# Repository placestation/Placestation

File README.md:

# PlaceStation

PlaceStation is a desktop pick-and-place machine for PCB assembly, manufactured by **Tejwani Industries Private Limited (TIPL)** in Maharashtra, India.

PlaceStation is a **derivative of the open-source [LumenPnP project by Opulo Inc.](https://github.com/opulo-inc/lumenpnp)** This repository contains the design source for all PlaceStation-specific modifications, released under the same open-source licenses as the upstream project.

If you are looking for the unmodified LumenPnP design files (frame, gantry, motherboard, feeders, etc.), please see the [upstream LumenPnP repository](https://github.com/opulo-inc/lumenpnp).

---

## What PlaceStation is

PlaceStation is sold as a finished pick-and-place machine for small electronics manufacturers, prototyping labs, and hardware startups in India and abroad. It is **based on LumenPnP v4** with the modifications listed below.

The PlaceStation product is sold commercially. The underlying design source — both upstream LumenPnP and the PlaceStation-specific modifications — is open source under CERN-OHL-W v2, GPLv3, and related licenses.

## Modifications in PlaceStation

For a detailed list see [CHANGES.md](./CHANGES.md). In brief:

1. **Sensorless homing (no endstop PCB)** — modified `x-motor-mount` removes the endstop cavity; X/Y endstop hardware is removed entirely; Marlin firmware patched for sensorless homing
2. **MGN12 linear rails throughout** — consistent rail size simplifies sourcing and assembly
3. **Motherboard manufactured by TIPL** — `mobo-REV05` design from Opulo, manufactured by TIPL with Opulo branding removed from silkscreen (license-compliant per CERN-OHL-W v2 §8.2)
4. **Datum board manufactured by TIPL** — Opulo's homing/calibration fiducial board, manufactured by TIPL with Opulo branding removed from silkscreen (same license-compliant debranding as the motherboard)
5. **Feeder PCB manufactured by TIPL** — Photon feeder board from Opulo, manufactured by TIPL with Opulo branding removed from silkscreen. This pass also inadvertently removed silkscreen artwork by Alethea "Stargirl" Flowers ([@theacodes](https://github.com/theacodes)) — see [CREDITS.md](./CREDITS.md#feeder-pcb-art-alethea-stargirl-flowers) for attribution
6. **Dual-color printed secondary fiducial** — replaces Opulo's PCB-based fiducial with a 3D-printed dual-extrusion part (black surround, white center dot)
7. **OpenPnP closed-loop feeder calibration plugin** — vision-based pocket calibration for Photon feeders, integrated into the `press-play-walk-away` branch of OpenPnP
8. **Custom Marlin firmware** — sensorless homing for X/Y plus speed-increment customizations

## Repository structure

```
.
├── README.md                        ← you are here
├── LICENSE                          ← umbrella license, points to per-component licenses
├── NOTICE                           ← attribution to all upstream projects
├── CHANGES.md                       ← detailed description of modifications
├── CREDITS.md                       ← all contributors and projects credited
├── licenses/
│   ├── CERN-OHL-W-v2.txt
│   ├── GPL-v3.txt
│   ├── MIT.txt
│   └── CC-BY-SA-4.0.txt
├── hardware/                        ← CAD modifications (CERN-OHL-W v2)
│   ├── x-motor-mount/
│   ├── mgn12-x-gantry/
│   └── secondary-fid-dual-color/
├── pcb/                             ← PCB modifications (CERN-OHL-W v2)
│   ├── mobo-REV05-debranded/
│   └── datum-board-debranded/
├── firmware/                        ← Firmware (GPLv3)
│   └── marlin/                      ← (placeholder, sources uploaded separately)
├── software/                        ← OpenPnP plugins and configs
│   └── openpnp/                     ← see also linked fork repository
└── reference/
    └── placestation-full-assembly/  ← Fusion exports of the whole machine (optional)
```

## How to buy a PlaceStation

Visit [placestation.in](https://placestation.in).

## How to build your own from this source

This repository contains only the **PlaceStation modifications**. To build a complete machine you also need the unmodified upstream LumenPnP files. The recommended flow is:

1. Clone the upstream LumenPnP repository: `git clone https://github.com/opulo-inc/lumenpnp`
2. Clone this repository: `git clone https://github.com/placestation/Placestation`
3. Use parts from the upstream repo unless this repo has a replacement for them
4. For firmware: see `firmware/marlin/README.md`
5. For software: see `software/openpnp/README.md`

We are a small team and cannot offer free build support. Commercial machines come with full assembly and support from TIPL.

## Licenses

This project uses multiple licenses for different components. See [LICENSE](./LICENSE) for the umbrella summary and [licenses/](./licenses/) for full license texts.

- **Hardware (CAD, PCB):** CERN-OHL-W v2
- **Firmware (Marlin fork):** GPLv3
- **Software (OpenPnP plugin):** GPLv3 (inherited from OpenPnP)
- **Software (PlaceStation tools and configs):** MIT
- **Documentation:** CC BY-SA 4.0

## Attribution

PlaceStation builds on the work of many open-source projects and individuals. See [CREDITS.md](./CREDITS.md) for the full list.

Particular thanks to:
- **Opulo Inc. / Stephen Hawes** for LumenPnP and the upstream Marlin fork
- **The OpenPnP project** and contributors, especially **Jorropo** for the `press-play-walk-away` branch
- **Richard Klingler** and **PapaJ** for the CP40 nozzle holder design
- **The Photon firmware project** for the Photon feeder protocol
- **Alethea "Stargirl" Flowers** ([@theacodes](https://github.com/theacodes)) for the original feeder PCB silkscreen artwork
- **The Marlin Firmware project** for the base firmware

## Contact

Tejwani Industries Private Limited
GSTIN: 27AALCT0935H1Z6
Maharashtra, India
Website: [placestation.in](https://placestation.in)

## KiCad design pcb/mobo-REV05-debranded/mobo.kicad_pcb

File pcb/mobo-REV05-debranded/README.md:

# mobo-REV05-debranded

PlaceStation motherboard — Opulo `mobo-REV05` design, manufactured by TIPL, with Opulo branding removed from the silkscreen layer.

## What changed

**Silkscreen only.** The Opulo wordmark and logo have been removed from the silkscreen layer per CERN-OHL-W v2 §8.2, which requires removal of upstream trademarks when redistributing under a different brand.

Schematic, electrical layout, copper layers, drill files, BOM, component values, and functionality are **identical to upstream `mobo-REV05`**. This is not a redesign.

## Files

| File | Format | Description |
|------|--------|-------------|
| `mobo.kicad_pcb` | KiCad PCB | Board layout source |
| `mobo.kicad_pro` | KiCad project | Project file |

## Manufacturing

This board is manufactured by Tejwani Industries Private Limited (TIPL) under the CERN-OHL-W v2 license, which explicitly permits commercial manufacturing of covered hardware (§4.1).

## License

CERN-OHL-W v2 — see [`../../licenses/CERN-OHL-W-v2.txt`](../../licenses/CERN-OHL-W-v2.txt)

**Upstream:** `mobo-REV05` originally designed by Opulo Inc. ([github.com/opulo-inc/lumenpnp](https://github.com/opulo-inc/lumenpnp)), CERN-OHL-W v2. This file is a silkscreen-only derivative.

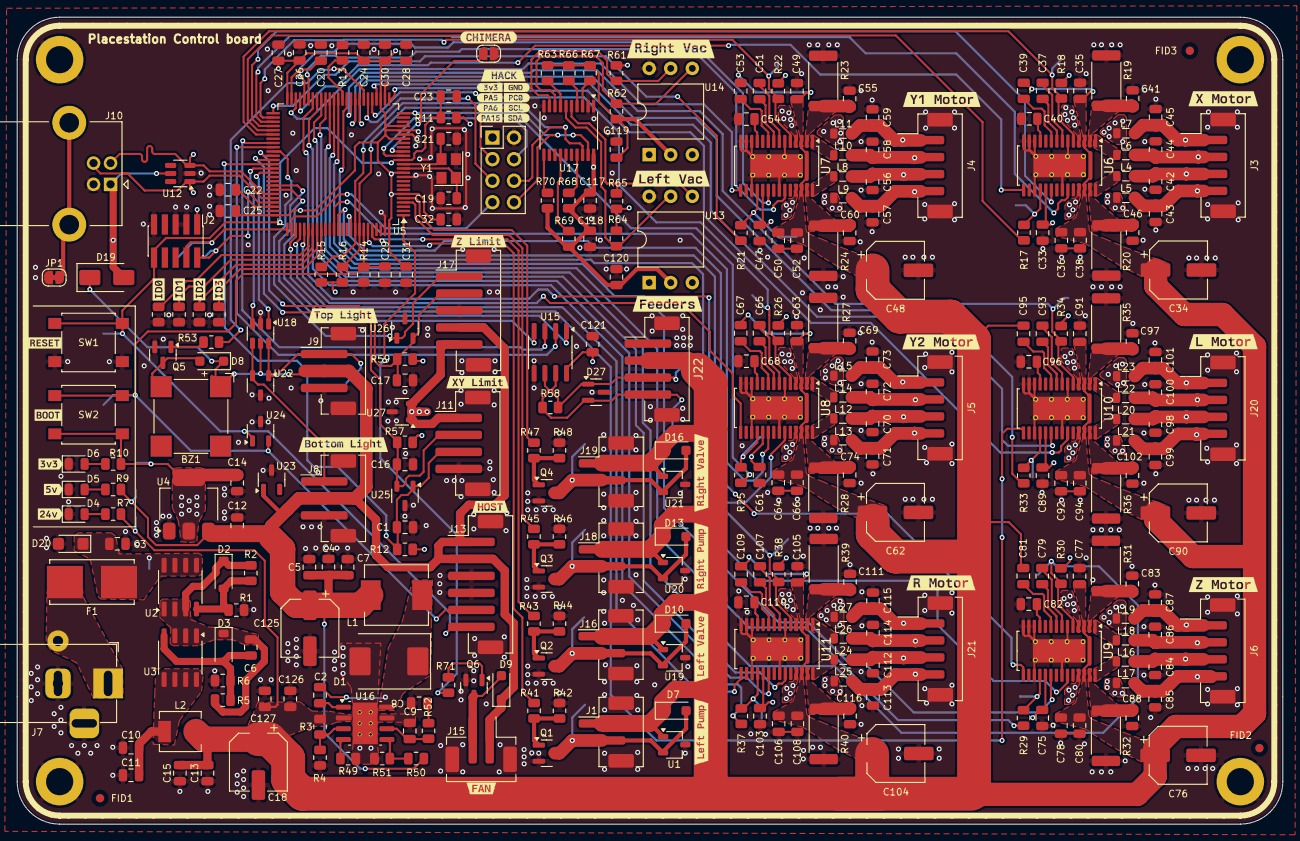
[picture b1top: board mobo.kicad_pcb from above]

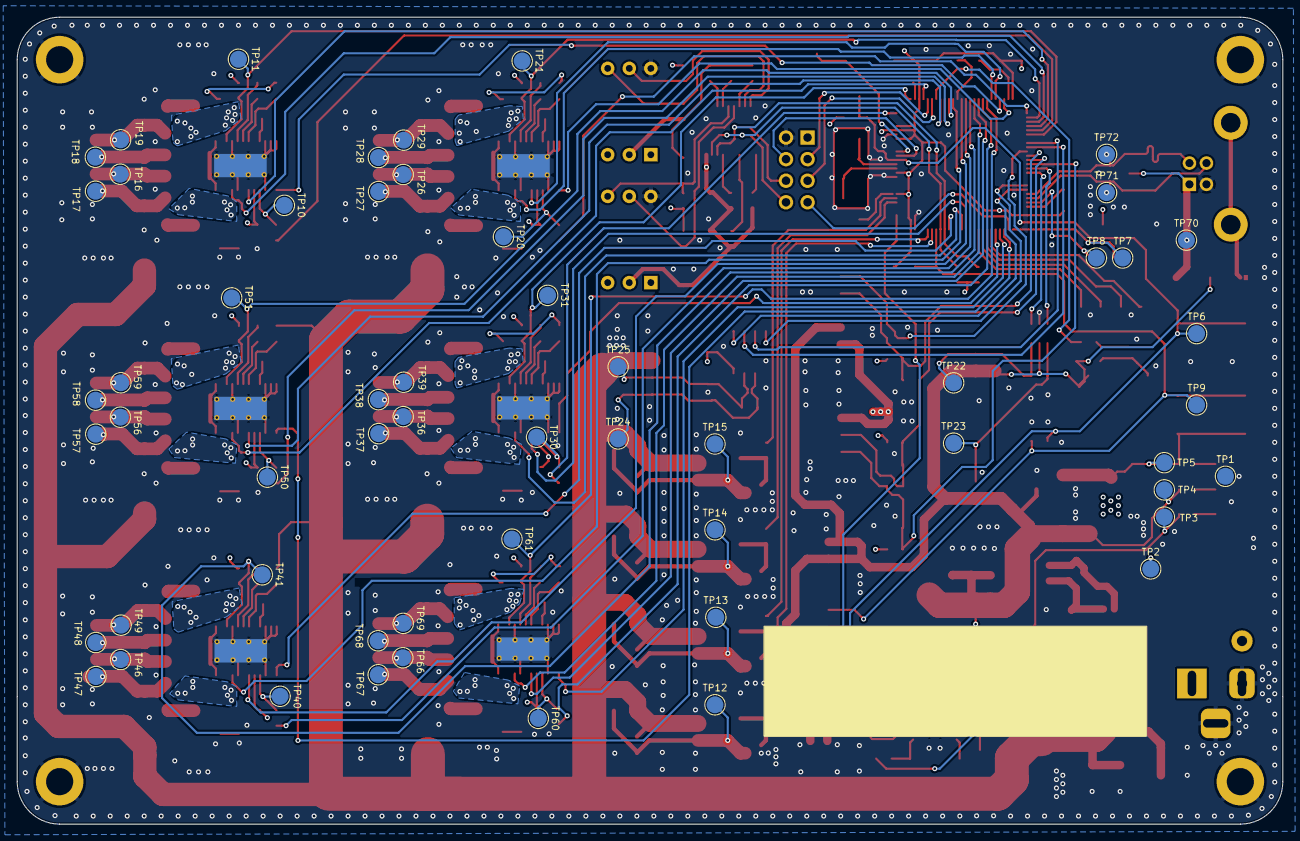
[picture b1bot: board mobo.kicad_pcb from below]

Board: 4 copper layers, 149.0 x 95.0 mm, 397 parts (56 on the bottom side), 206 nets.

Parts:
BZ1: Buzzer; MagneticBuzzer_CUI_CMT-8504-100-SMT
C1, C6, C16, C17, C23, C26, C27, C28, C29, C30, C31, C32, C33, C36, C38, C39, C41, C46, C47, C50, C52, C53, C55, C60, C61, C64, C66, C67, C69, C74, C75, C78, C80, C81, C83, C88, C89, C92, C94, C95, C97, C102, C103, C106, C108, C109, C111, C116, C117, C119, C120, C121: 100n; C_0805_2012Metric
C2: 0.1u; C_0805_2012Metric
C3, C4, C5, C7, C10, C11, C12, C13, C14, C15, C35, C49, C63, C77, C91, C105, C118, C126, C127: 10u; C_0805_2012Metric
C8: 4.7n; C_0805_2012Metric
C9: 47p; C_0805_2012Metric
C18, C34, C48, C62, C76, C90, C104, C125: 100u; CP_Elec_6.3x7.7
C19, C21: 10p; C_0805_2012Metric
C20, C22, C24, C25: 2u2; C_0805_2012Metric
C37, C51, C65, C79, C93, C107: 22n; C_0805_2012Metric
C40, C54, C68, C82, C96, C110: 4.7u; C_0805_2012Metric
C42, C43, C44, C45, C56, C57, C58, C59, C70, C71, C72, C73, C84, C85, C86, C87, C98, C99, C100, C101, C112, C113, C114, C115: 470p; C_0805_2012Metric
D1: B560C; D_SMC
D2, D3: BZT52C16; D_SOD-123
D4, D5, D6: Yellow; LED_0805_2012Metric
D7, D8, D9, D10, D13, D16: SM4007; D_SOD-123F
D19: SS34; D_SMA
D20: SMF28A; D_SMF
D27: SM712_SOT23; SOT-23
F1: Fuse; Fuseholder_Littelfuse_Nano2_154x
FID1, FID2, FID3: Fiducial; Fiducial_1mm_Mask2mm
H1, H2, H3, H4: MountingHole_Pad; MountingHole_3.2mm_M3_DIN965_Pad
J1, J16, J18, J19: FET; JST_PH_B2B-PH-SM4-TB_1x02-1MP_P2.00mm_Vertical
J2: SWD Header; PinHeader_2x05_P1.27mm_Vertical_SMD
J3, J4, J5, J6, J20, J21: MOTOR; JST_PH_B4B-PH-SM4-TB_1x04-1MP_P2.00mm_Vertical
J7: COMBO_POWER_JACK; BarrelJack_Horizontal
J8: BTM_LIGHT; JST_PH_B3B-PH-SM4-TB_1x03-1MP_P2.00mm_Vertical
J9: TOP_LIGHT; JST_PH_B3B-PH-SM4-TB_1x03-1MP_P2.00mm_Vertical
J10: USB_B; USB_B_Lumberg_2411_02_Horizontal
J11: XY_LIMIT; JST_PH_B4B-PH-SM4-TB_1x04-1MP_P2.00mm_Vertical
J13: HOST; JST_PH_B6B-PH-SM4-TB_1x06-1MP_P2.00mm_Vertical
J14: HACK_HEADER; PinHeader_2x04_P2.54mm_Vertical
J15: FAN; JST_PH_B2B-PH-SM4-TB_1x02-1MP_P2.00mm_Vertical
J17: Z_LIMIT; JST_PH_B5B-PH-SM4-TB_1x05-1MP_P2.00mm_Vertical
J22: FEEDERS; JST_PH_B4B-PH-SM4-TB_1x04-1MP_P2.00mm_Vertical
JP1: SHIELD_GND; SolderJumper-2_P1.3mm_Bridged_RoundedPad1.0x1.5mm
JP2: CHIMERA_JUMPER; SolderJumper-2_P1.3mm_Open_RoundedPad1.0x1.5mm
L1: 7.2u; L_Sunlord_MWSA0603S
L2: 2.2u; L_Sunlord_MWSA0402S
L4, L5, L6, L7, L8, L9, L10, L11, L12, L13, L14, L15, L16, L17, L18, L19, L20, L21, L22, L23, L24, L25, L26, L27: L_Ferrite; L_0805_2012Metric
Q1, Q2, Q3, Q4, Q5, Q6: AO3400A; SOT-23
R1, R3, R6, R7, R11, R13, R14, R18, R22, R26, R30, R34, R38, R42, R44, R46, R48, R51, R63, R66, R67, R68, R69, R70: 10k; R_0805_2012Metric
R2, R5, R15, R16: 4.7k; R_0805_2012Metric
R4, R9: 2.7k; R_0805_2012Metric
R8, R54, R55, R56: 0R; R_0805_2012Metric
R10, R17, R21, R25, R29, R33, R37: 1k; R_0805_2012Metric
R12, R57, R59: 10K; R_0805_2012Metric
R19, R20, R23, R24, R27, R28, R31, R32, R35, R36, R39, R40: 120m; R_2512_6332Metric
R41, R43, R45, R47, R58: 120; R_0805_2012Metric
R49: 243k; R_0805_2012Metric
R50: 53.6k; R_0805_2012Metric
R52: 16.9k; R_0805_2012Metric
R53, R71: 120R; R_0805_2012Metric
R61, R62, R64, R65: 4k7; R_0805_2012Metric
SW1, SW2: SW_Push; SW_SPST_B3S-1000
TP1, TP2, TP3, TP4, TP5, TP6, TP7, TP8, TP9, TP10, TP11, TP12, TP13, TP14, TP15, TP16, TP17, TP18, TP19, TP20, TP21, TP22, TP23, TP24, TP25, TP26, TP27, TP28, TP29, TP30, TP31, TP36, TP37, TP38, TP39, TP40, TP41, TP46, TP47, TP48, TP49, TP50, TP51, TP56, TP57, TP58, TP59, TP60, TP61, TP66, TP67, TP68, TP69, TP70, TP71, TP72: TestPoint; TestPoint_Pad_D2.0mm
U1, U19, U20, U21: TSOT-23
U2, U3: FDS4435BZ; SO-8_3.9x4.9mm_P1.27mm
U4: AP1117-33; SOT-223-3_TabPin2
U5: STM32F407VETx; LQFP-100_14x14mm_P0.5mm
U6, U7, U8, U9, U10, U11: TMC2226-SA; HTSSOP-28-1EP_4.4x9.7mm_P0.65mm_EP2.75x6.2mm_ThermalVias
U12: SRV05-4; SOT-23-6
U13, U14: XGZP6857D; DIP-6_W10.16mm
U15: MAX3078E; SOIC-8_3.9x4.9mm_P1.27mm
U16: TPS54560BDDA; Texas_R-PDSO-G8_EP2.95x4.9mm_Mask2.4x3.1mm_ThermalVias
U17: PCA9545A; TSSOP-20_4.4x6.5mm_P0.65mm
U18: SN74LVC2G34; SOT-23-6
U22, U23: PESD5V2S2UT; SOT-23-3
U24, U25, U26, U27: PESD3V3S2UT; SOT-23-3
Y1: 8MHz; Crystal_SMD_3225-4Pin_3.2x2.5mm
kibuzzard-65DCF286: G***; kibuzzard-65DCF286
kibuzzard-65E24FAE: G***; kibuzzard-65E24FAE
kibuzzard-65E215D8: G***; kibuzzard-65E215D8
kibuzzard-65E215EC: G***; kibuzzard-65E215EC
kibuzzard-65E240B2: G***; kibuzzard-65E240B2
kibuzzard-65E241C9: G***; kibuzzard-65E241C9
kibuzzard-65E2151D: G***; kibuzzard-65E2151D
kibuzzard-65E2155B: G***; kibuzzard-65E2155B
kibuzzard-65E2156F: G***; kibuzzard-65E2156F
kibuzzard-65E2408C: G***; kibuzzard-65E2408C
kibuzzard-65E2409D: G***; kibuzzard-65E2409D
kibuzzard-65E2504F: G***; kibuzzard-65E2504F
kibuzzard-65E24108: G***; kibuzzard-65E24108
kibuzzard-65E24112: G***; kibuzzard-65E24112
kibuzzard-65E24141: G***; kibuzzard-65E24141
kibuzzard-65E25035: G***; kibuzzard-65E25035
kibuzzard-65E25071: G***; kibuzzard-65E25071
kibuzzard-65F1FEA3: G***; kibuzzard-65F1FEA3
kibuzzard-6585C0AF: G***; kibuzzard-6585C0AF
kibuzzard-6585C0D3: G***; kibuzzard-6585C0D3
kibuzzard-6585C08F: G***; kibuzzard-6585C08F
kibuzzard-6585C058: G***; kibuzzard-6585C058
kibuzzard-6606EA2E: G***; kibuzzard-6606EA2E
kibuzzard-6606EA4F: G***; kibuzzard-6606EA4F
kibuzzard-6606EA6E: G***; kibuzzard-6606EA6E
kibuzzard-65709CC6: G***; kibuzzard-65709CC6
kibuzzard-65709E62: G***; kibuzzard-65709E62
kibuzzard-65848E86: G***; kibuzzard-65848E86
kibuzzard-65848E91: G***; kibuzzard-65848E91
kibuzzard-65848EB6: G***; kibuzzard-65848EB6
kibuzzard-65848FCC: G***; kibuzzard-65848FCC
kibuzzard-65848FD5: G***; kibuzzard-65848FD5
kibuzzard-65848FDC: G***; kibuzzard-65848FDC
kibuzzard-65848FE3: G***; kibuzzard-65848FE3
kibuzzard-65848FE9: G***; kibuzzard-65848FE9
kibuzzard-65848FEF: G***; kibuzzard-65848FEF
kibuzzard-660711AC: G***; kibuzzard-660711AC
kibuzzard-66071149: G***; kibuzzard-66071149

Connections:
+3.3V: C14.1, C24.1, C25.1, C26.1, C27.1, C28.1, C30.1, C31.1, C32.1, C33.2, C47.2, C61.2, C75.2, C89.2, C103.2, C117.1, C118.1, C119.1, C120.1, C121.2, J2.1 (VTref), J11.1, J14.1, J17.5, R10.1, R11.1, R12.2, R15.1, R16.1, R18.1, R22.1, R26.1, R30.1, R34.1, R38.1, R57.2, R59.2, R61.2, R62.2, R63.1, R64.1, R65.1, R66.1, R67.1, R68.2, R69.2, R70.2, SW2.2, TP5.1, U4.2 (VO), U5.6 (VBAT), U5.11 (VDD), U5.19 (VDD), U5.21 (VREF+), U5.22 (VDDA), U5.28 (VDD), U5.50 (VDD), U5.75 (VDD), U5.100 (VDD), U6.19 (VCC_IO), U7.19 (VCC_IO), U8.19 (VCC_IO), U9.19 (VCC_IO), U10.19 (VCC_IO), U11.19 (VCC_IO), U13.2 (VDD), U14.2 (VDD), U15.8 (VCC), U17.20 (VDD), U27.1, U27.2
+5V: BZ1.1 (-), C4.2, C5.2, C7.2, C12.1, C125.1, D8.1 (K), D9.1 (K), D19.1 (K), J8.2, J9.2, J13.1, J13.2, J15.1, J17.4, L1.2, R9.1, R50.1, TP4.1, U4.3 (VI), U18.5 (VCC), U23.1
/Lighting/BTM_LIGHT: U5.64 (PC7), U18.3 (2A)
/Microcontroller/AUX: J17.1, U5.60 (PD13), U26.1
/Microcontroller/BOOT1: R13.1, U5.37 (PB2)
/Microcontroller/BUZZER: R53.1, U5.32 (PA7)
/Microcontroller/CHIMERA: JP2.1 (A), U5.16 (PC1)
/Microcontroller/FAN: R71.1, U5.1 (PE2)
/Microcontroller/I2C_SCL: J14.6, R15.2, U5.92 (PB6), U17.18 (SCL)
/Microcontroller/I2C_SDA: J14.8, R16.2, U5.93 (PB7), U17.19 (SDA)
/Microcontroller/ID0: R8.2, U5.81 (PD0)
/Microcontroller/ID1: R54.2, U5.82 (PD1)
/Microcontroller/ID2: R55.2, U5.83 (PD2)
/Microcontroller/ID3: R56.2, U5.84 (PD3)
/Microcontroller/LUMEN_AUX_A1: J14.4, U5.15 (PC0)
/Microcontroller/LUMEN_AUX_PWM1: J14.3, U5.30 (PA5)
/Microcontroller/LUMEN_AUX_PWM2: J14.5, U5.31 (PA6)
/Microcontroller/LUMEN_AUX_PWM3: J14.7, U5.77 (PA15)
/Microcontroller/MOS1: R41.2, U5.95 (PB8)
/Microcontroller/MOS2: R43.2, U5.96 (PB9)
/Microcontroller/MOS3: R45.2, U5.4 (PE5)
/Microcontroller/MOS4: R47.2, U5.5 (PE6)
/Microcontroller/PA2: R25.2, U5.25 (PA2)
/Microcontroller/PA3: R26.2, TP31.1, U5.26 (PA3), U8.5 (~EN)
/Microcontroller/PA4: U5.29 (PA4), U10.23 (DIR)
/Microcontroller/PB0: R34.2, TP51.1, U5.35 (PB0), U10.5 (~EN)
/Microcontroller/PB1: U5.36 (PB1), U9.23 (DIR)
/Microcontroller/PB5: U5.91 (PB5), U9.15 (DIAG)
/Microcontroller/PB10: U5.47 (PB10), U6.15 (DIAG)
/Microcontroller/PB11: U5.48 (PB11), U7.15 (DIAG)
/Microcontroller/PB12: R21.2, U5.51 (PB12)
/Microcontroller/PB13: R22.2, TP21.1, U5.52 (PB13), U7.5 (~EN)
/Microcontroller/PB14: U5.53 (PB14), U6.23 (DIR)
/Microcontroller/PB15: U5.54 (PB15), U6.20 (STEP)
/Microcontroller/PC4: U5.33 (PC4), U10.20 (STEP)
/Microcontroller/PC5: R33.2, U5.34 (PC5)
/Microcontroller/PC10: U5.78 (PC10), U10.15 (DIAG)
/Microcontroller/PC11: U5.79 (PC11), U11.15 (DIAG)
/Microcontroller/PC12: U5.80 (PC12), U8.15 (DIAG)
/Microcontroller/PD6: U5.87 (PD6), U8.20 (STEP)
/Microcontroller/PD7: U5.88 (PD7), U8.23 (DIR)
/Microcontroller/PD9: R18.2, TP11.1, U5.56 (PD9), U6.5 (~EN)
/Microcontroller/PE7: U5.38 (PE7), U9.20 (STEP)
/Microcontroller/PE8: R29.2, U5.39 (PE8)
/Microcontroller/PE9: R30.2, TP41.1, U5.40 (PE9), U9.5 (~EN)
/Microcontroller/PE10: U5.41 (PE10), U11.23 (DIR)
/Microcontroller/PE11: U5.42 (PE11), U11.20 (STEP)
/Microcontroller/PE12: R37.2, U5.43 (PE12)
/Microcontroller/PE13: R38.2, TP61.1, U5.44 (PE13), U11.5 (~EN)
/Microcontroller/PE14: U5.45 (PE14), U7.23 (DIR)
/Microcontroller/PE15: U5.46 (PE15), U7.20 (STEP)
/Microcontroller/RS485_DE: U5.58 (PD11), U15.3 (DE)
/Microcontroller/RS485_RE: U5.59 (PD12), U15.2 (~RE)
/Microcontroller/RS485_RX: U5.69 (PA10), U15.1 (RO)
/Microcontroller/RS485_TX: U5.68 (PA9), U15.4 (DI)
/Microcontroller/SWCLK: J2.4 (SWDCLK/TCK), TP7.1, U5.76 (PA14)
/Microcontroller/SWDIO: J2.2 (SWDIO/TMS), TP8.1, U5.72 (PA13)
/Microcontroller/USB_D+: J10.3 (D+), TP71.1, U5.71 (PA12), U12.1 (IO1)
/Microcontroller/USB_D-: J10.2 (D-), TP72.1, U5.70 (PA11), U12.3 (IO2)
/Microcontroller/X_LIMIT: C1.1, J11.3, R12.1, U5.63 (PC6), U25.1
/Microcontroller/X_UART: R17.2, U5.55 (PD8)
/Microcontroller/Y_LIMIT: C16.1, J11.2, R57.1, U5.62 (PD15), U25.2
/Microcontroller/Z_LIMIT: C17.1, J17.2, R59.1, U5.61 (PD14), U26.2
/Motor L/5VOUT: C96.2, U10.11 (5VOUT)
/Motor L/A1: C98.2, J20.3, L20.2, TP56.1
/Motor L/A2: C99.1, J20.4, L21.2, TP57.1
/Motor L/B1: C100.2, J20.2, L22.2, TP58.1
/Motor L/B2: C101.1, J20.1, L23.2, TP59.1
/Motor R/5VOUT: C110.2, U11.11 (5VOUT)
/Motor R/A1: C112.2, J21.3, L24.2, TP66.1
/Motor R/A2: C113.1, J21.4, L25.2, TP67.1
/Motor R/B1: C114.2, J21.2, L26.2, TP68.1
/Motor R/B2: C115.1, J21.1, L27.2, TP69.1
/Motor X/5VOUT: C40.2, U6.11 (5VOUT)
/Motor X/A1: C42.2, J3.3, L4.2, TP16.1
/Motor X/A2: C43.1, J3.4, L5.2, TP17.1
/Motor X/B1: C44.2, J3.2, L6.2, TP18.1
/Motor X/B2: C45.1, J3.1, L7.2, TP19.1
/Motor Y1/5VOUT: C54.2, U7.11 (5VOUT)
/Motor Y1/A1: C56.2, J4.3, L8.2, TP26.1
/Motor Y1/A2: C57.1, J4.4, L9.2, TP27.1
/Motor Y1/B1: C58.2, J4.2, L10.2, TP28.1
/Motor Y1/B2: C59.1, J4.1, L11.2, TP29.1
/Motor Y2/5VOUT: C68.2, U8.11 (5VOUT)
/Motor Y2/A1: C70.2, J5.3, L12.2, TP36.1
/Motor Y2/A2: C71.1, J5.4, L13.2, TP37.1
/Motor Y2/B1: C72.2, J5.2, L14.2, TP38.1
/Motor Y2/B2: C73.1, J5.1, L15.2, TP39.1
/Motor Z/5VOUT: C82.2, U9.11 (5VOUT)
/Motor Z/A1: C84.2, J6.3, L16.2, TP46.1
/Motor Z/A2: C85.1, J6.4, L17.2, TP47.1
/Motor Z/B1: C86.2, J6.2, L18.2, TP48.1
/Motor Z/B2: C87.1, J6.1, L19.2, TP49.1
/Power/POWER_SUPPLY: F1.1, J7.1, J7.4
/Power/VIN: C3.2, D20.1 (A1), F1.2, TP2.1, U2.5 (D), U2.6 (D), U2.7 (D), U2.8 (D)
/RS485/RS-485+: D27.2 (A2), J22.4, R58.1, TP24.1, U15.6 (A)
/RS485/RS-485-: D27.1 (A1), J22.3, R58.2, TP25.1, U15.7 (B)
/Vacuum sensors/SC0: R64.2, U13.5 (SCL), U17.6 (SC0)
/Vacuum sensors/SC1: R61.1, U14.5 (SCL), U17.9 (SC1)
/Vacuum sensors/SD0: R65.2, U13.4 (SDA), U17.5 (SD0)
/Vacuum sensors/SD1: R62.1, U14.4 (SDA), U17.8 (SD1)
BOOT: C29.1, J13.5, R14.1, SW2.1, TP9.1, U5.94 (BOOT0), U24.2
GND: C1.2, C3.1, C4.1, C5.1, C7.1, C8.1, C9.1, C10.1, C11.1, C12.2, C13.1, C14.2, C15.1, C16.2, C17.2, C18.2, C19.2, C20.2, C21.2, C22.2, C23.2, C24.2, C25.2, C26.2, C27.2, C28.2, C29.2, C30.2, C31.2, C32.2, C33.1, C34.2, C35.1, C36.1, C38.1, C40.1, C41.1, C42.1, C43.2, C44.1, C45.2, C46.1, C47.1, C48.2, C49.1, C50.1, C52.1, C54.1, C55.1, C56.1, C57.2, C58.1, C59.2, C60.1, C61.1, C62.2, C63.1, C64.1, C66.1, C68.1, C69.1, C70.1, C71.2, C72.1, C73.2, C74.1, C75.1, C76.2, C77.1, C78.1, C80.1, C82.1, C83.1, C84.1, C85.2, C86.1, C87.2, C88.1, C89.1, C90.2, C91.1, C92.1, C94.1, C96.1, C97.1, C98.1, C99.2, C100.1, C101.2, C102.1, C103.1, C104.2, C105.1, C106.1, C108.1, C110.1, C111.1, C112.1, C113.2, C114.1, C115.2, C116.1, C117.2, C118.2, C119.2, C120.2, C121.1, C125.2, C126.1, C127.1, D1.2 (A), D4.1 (K), D5.1 (K), D6.1 (K), D20.2 (A2), D27.3 (common), H1.1, H2.1, H3.1, H4.1, J1.MP (MountPin), J2.3 (GND), J2.5 (GND), J2.9 (GNDDetect), J3.MP (MountPin), J4.MP (MountPin), J5.MP (MountPin), J6.MP (MountPin), J7.2, J7.3, J8.3, J8.MP (MountPin), J9.3, J9.MP (MountPin), J10.4 (GND), J11.4, J11.MP (MountPin), J13.3, J13.4, J13.MP (MountPin), J14.2, J15.MP (MountPin), J16.MP (MountPin), J17.3, J17.MP (MountPin), J18.MP (MountPin), J19.MP (MountPin), J20.MP (MountPin), J21.MP (MountPin), J22.1, J22.MP (MountPin), JP1.2 (B), JP2.2 (B), Q1.2 (S), Q2.2 (S), Q3.2 (S), Q4.2 (S), Q5.2 (S), Q6.2 (S), R1.2, R4.2, R6.2, R8.1, R13.2, R14.2, R19.2, R20.2, R23.2, R24.2, R27.2, R28.2, R31.2, R32.2, R35.2, R36.2, R39.2, R40.2, R42.1, R44.1, R46.1, R48.1, R49.2, R51.2, R54.1, R55.1, R56.1, SW1.1, TP1.1, U1.3, U4.1 (GND), U5.10 (VSS), U5.20 (VSSA), U5.27 (VSS), U5.74 (VSS), U5.99 (VSS), U6.6 (GND), U6.12 (MS1_AD0), U6.13 (NC), U6.14 (MS2_AD1), U6.17 (CLK), U6.22 (GND), U6.29 (GND), U7.6 (GND), U7.12 (MS1_AD0), U7.13 (NC), U7.14 (MS2_AD1), U7.17 (CLK), U7.22 (GND), U7.29 (GND), U8.6 (GND), U8.12 (MS1_AD0), U8.13 (NC), U8.14 (MS2_AD1), U8.17 (CLK), U8.22 (GND), U8.29 (GND), U9.6 (GND), U9.12 (MS1_AD0), U9.13 (NC), U9.14 (MS2_AD1), U9.17 (CLK), U9.22 (GND), U9.29 (GND), U10.6 (GND), U10.12 (MS1_AD0), U10.13 (NC), U10.14 (MS2_AD1), U10.17 (CLK), U10.22 (GND), U10.29 (GND), U11.6 (GND), U11.12 (MS1_AD0), U11.13 (NC), U11.14 (MS2_AD1), U11.17 (CLK), U11.22 (GND), U11.29 (GND), U12.2 (VN), U13.6 (GND), U14.6 (GND), U15.5 (GND), U16.7 (GND), U16.9 (GND), U17.1 (A0), U17.2 (A1), U17.10 (VSS), U18.2 (GND), U19.3, U20.3, U21.3, U22.3, U23.3, U24.3, U25.3, U26.3, U27.3, Y1.2, Y1.4
unnamed: BZ1.2 (+), D8.2 (A), Q5.3 (D)
unnamed: C8.2, R52.2
unnamed: C10.2, C11.2, L2.1, U3.5 (D), U3.6 (D), U3.7 (D), U3.8 (D)
unnamed: C2.1, D1.1 (K), L1.1, U16.8 (SW)
unnamed: D2.2 (A), R1.1, R2.2, U2.4 (G)
unnamed: C6.2, D2.1 (K), D3.1 (K), R2.1, R5.1, U2.1 (S), U2.2 (S), U2.3 (S), U3.1 (S), U3.2 (S), U3.3 (S)
unnamed: C6.1, D3.2 (A), R5.2, R6.1, U3.4 (G)
unnamed: D4.2 (A), R7.2
unnamed: D5.2 (A), R9.2
unnamed: D6.2 (A), R10.2
unnamed: D7.2 (A), J1.2, Q1.3 (D), TP12.1, U1.2
unnamed: D9.2 (A), J15.2, Q6.3 (D)
unnamed: D10.2 (A), J16.2, Q2.3 (D), TP13.1, U19.2
unnamed: D13.2 (A), J18.2, Q3.3 (D), TP14.1, U20.2
unnamed: D16.2 (A), J19.2, Q4.3 (D), TP15.1, U21.2
unnamed: J8.1, TP23.1, U18.4 (2Y), U22.2
unnamed: J9.1, TP22.1, U18.6 (1Y), U22.1
unnamed: J10.5 (Shield), JP1.1 (A)
unnamed: Q1.1 (G), R41.1, R42.2
unnamed: Q2.1 (G), R43.1, R44.2
unnamed: Q3.1 (G), R45.1, R46.2
unnamed: Q4.1 (G), R47.1, R48.2
unnamed: Q5.1 (G), R53.2
unnamed: Q6.1 (G), R71.2
unnamed: C19.1, U5.12 (PH0), Y1.1
unnamed: C21.1, U5.13 (PH1), Y1.3
unnamed: C20.1, U5.49 (VCAP_1)
unnamed: C22.1, U5.73 (VCAP_2)
unnamed: C46.2, R20.1, U6.27 (BRA)
unnamed: C41.2, R19.1, U6.2 (BRB)
unnamed: C37.2, U6.8 (CPI)
unnamed: C37.1, U6.7 (CPO)
unnamed: L4.1, U6.28 (OA1)
unnamed: L5.1, U6.25 (OA2)
unnamed: L6.1, U6.1 (OB1)
unnamed: L7.1, U6.4 (OB2)
unnamed: R17.1, TP10.1, U6.18 (PDN_UART)
unnamed: C39.1, U6.9 (VCP)
unnamed: C60.2, R24.1, U7.27 (BRA)
unnamed: C55.2, R23.1, U7.2 (BRB)
unnamed: C51.2, U7.8 (CPI)
unnamed: C51.1, U7.7 (CPO)
unnamed: L8.1, U7.28 (OA1)
unnamed: L9.1, U7.25 (OA2)
unnamed: L10.1, U7.1 (OB1)
unnamed: L11.1, U7.4 (OB2)
unnamed: R21.1, TP20.1, U7.18 (PDN_UART)
unnamed: C53.1, U7.9 (VCP)
unnamed: C74.2, R28.1, U8.27 (BRA)
unnamed: C69.2, R27.1, U8.2 (BRB)
unnamed: C65.2, U8.8 (CPI)
unnamed: C65.1, U8.7 (CPO)
unnamed: L12.1, U8.28 (OA1)
unnamed: L13.1, U8.25 (OA2)
unnamed: L14.1, U8.1 (OB1)
unnamed: L15.1, U8.4 (OB2)
unnamed: R25.1, TP30.1, U8.18 (PDN_UART)
unnamed: C67.1, U8.9 (VCP)
unnamed: C88.2, R32.1, U9.27 (BRA)
unnamed: C83.2, R31.1, U9.2 (BRB)
unnamed: C79.2, U9.8 (CPI)
unnamed: C79.1, U9.7 (CPO)
unnamed: L16.1, U9.28 (OA1)
unnamed: L17.1, U9.25 (OA2)
unnamed: L18.1, U9.1 (OB1)
unnamed: L19.1, U9.4 (OB2)
unnamed: R29.1, TP40.1, U9.18 (PDN_UART)
unnamed: C81.1, U9.9 (VCP)
unnamed: C102.2, R36.1, U10.27 (BRA)
unnamed: C97.2, R35.1, U10.2 (BRB)
unnamed: C93.2, U10.8 (CPI)
unnamed: C93.1, U10.7 (CPO)
unnamed: L20.1, U10.28 (OA1)
unnamed: L21.1, U10.25 (OA2)
unnamed: L22.1, U10.1 (OB1)
unnamed: L23.1, U10.4 (OB2)
unnamed: R33.1, TP50.1, U10.18 (PDN_UART)
unnamed: C95.1, U10.9 (VCP)
unnamed: C116.2, R40.1, U11.27 (BRA)
unnamed: C111.2, R39.1, U11.2 (BRB)
unnamed: C107.2, U11.8 (CPI)
unnamed: C107.1, U11.7 (CPO)
unnamed: L24.1, U11.28 (OA1)
unnamed: L25.1, U11.25 (OA2)
unnamed: L26.1, U11.1 (OB1)
unnamed: L27.1, U11.4 (OB2)
unnamed: R37.1, TP60.1, U11.18 (PDN_UART)
unnamed: C109.1, U11.9 (VCP)
unnamed: C2.2, U16.1 (BOOT)
unnamed: C9.2, R52.1, U16.6 (COMP)
unnamed: R3.2, R4.1, U16.3 (EN)
unnamed: R50.2, R51.1, U16.5 (FB)
unnamed: R49.1, U16.4 (RT/CLK)
unnamed: R66.2, U17.4 (_INT0_)
unnamed: R63.2, U17.7 (_INT1_)
unnamed: R70.1, U17.11 (_INT2_)
unnamed: R69.1, U17.14 (_INT3_)
unnamed: R68.1, U17.17 (_INT_)
unnamed: R67.2, U17.3 (_RESET_)
RESET: C23.1, J2.10 (~RESET), J13.6, R11.2, SW1.2, TP6.1, U5.14 (NRST), U24.1
TOP_LIGHT: U5.65 (PC8), U18.1 (1A)
VBUS: D19.2 (A), J10.1 (VBUS), TP70.1, U12.5 (VP)
VDC: C13.2, C15.2, C18.1, C34.1, C35.2, C36.2, C38.2, C39.2, C48.1, C49.2, C50.2, C52.2, C53.2, C62.1, C63.2, C64.2, C66.2, C67.2, C76.1, C77.2, C78.2, C80.2, C81.2, C90.1, C91.2, C92.2, C94.2, C95.2, C104.1, C105.2, C106.2, C108.2, C109.2, C126.2, C127.2, D7.1 (K), D10.1 (K), D13.1 (K), D16.1 (K), J1.1, J16.1, J18.1, J19.1, J22.2, L2.2, R3.1, R7.1, TP3.1, U1.1, U6.3 (VS), U6.26 (VS), U7.3 (VS), U7.26 (VS), U8.3 (VS), U8.26 (VS), U9.3 (VS), U9.26 (VS), U10.3 (VS), U10.26 (VS), U11.3 (VS), U11.26 (VS), U16.2 (VIN), U19.1, U20.1, U21.1

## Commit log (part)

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2025-09-26 Create CAD
2026-05-13 Initial PlaceStation open-source release
    Replaces previous repo contents with the complete PlaceStation source
    for v4.x machines: hardware mods (x-motor-mount, MGN12 gantry, dual-color
    secondary fiducial), PCB silkscreen debrand of Opulo's mobo-REV05,
    OpenPnP closed-loop feeder calibration plugin, gear-ratio calibration
    tool, and machine config. Marlin firmware sources to follow.
    Proper attribution to LumenPnP (Opulo), OpenPnP, Marlin, Photon firmware,
2026-05-13 Add license texts (CERN-OHL-W v2, GPLv3, MIT, CC BY-SA 4.0)
